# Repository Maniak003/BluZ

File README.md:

<!DOCTYPE html>
<html lang="en" data-color-mode="auto" data-light-theme="light" data-dark-theme="dark">
  <head>
    <meta charset="utf-8">
  </head>
    <body class="logged-in env-production page-responsive page-blob" style="word-wrap: break-word;">
      <p> BluZ Scintillation gamma spectrometer based on SiPM Sensl FC60035/FJ60035, Broadcom AFBR-S4N66C013, EQR15 11-6060D-S & NaI(Tl) or SrI2(Eu). Bluetooth 5.x<br>For discussion https://t.me/+mRf25RTZtPs3NTli</p>
      <a href=https://github.com/Maniak003/BluZ/releases/download/BluZ/BluZ-release.apk> Application in release </a>

    </body>
</html>

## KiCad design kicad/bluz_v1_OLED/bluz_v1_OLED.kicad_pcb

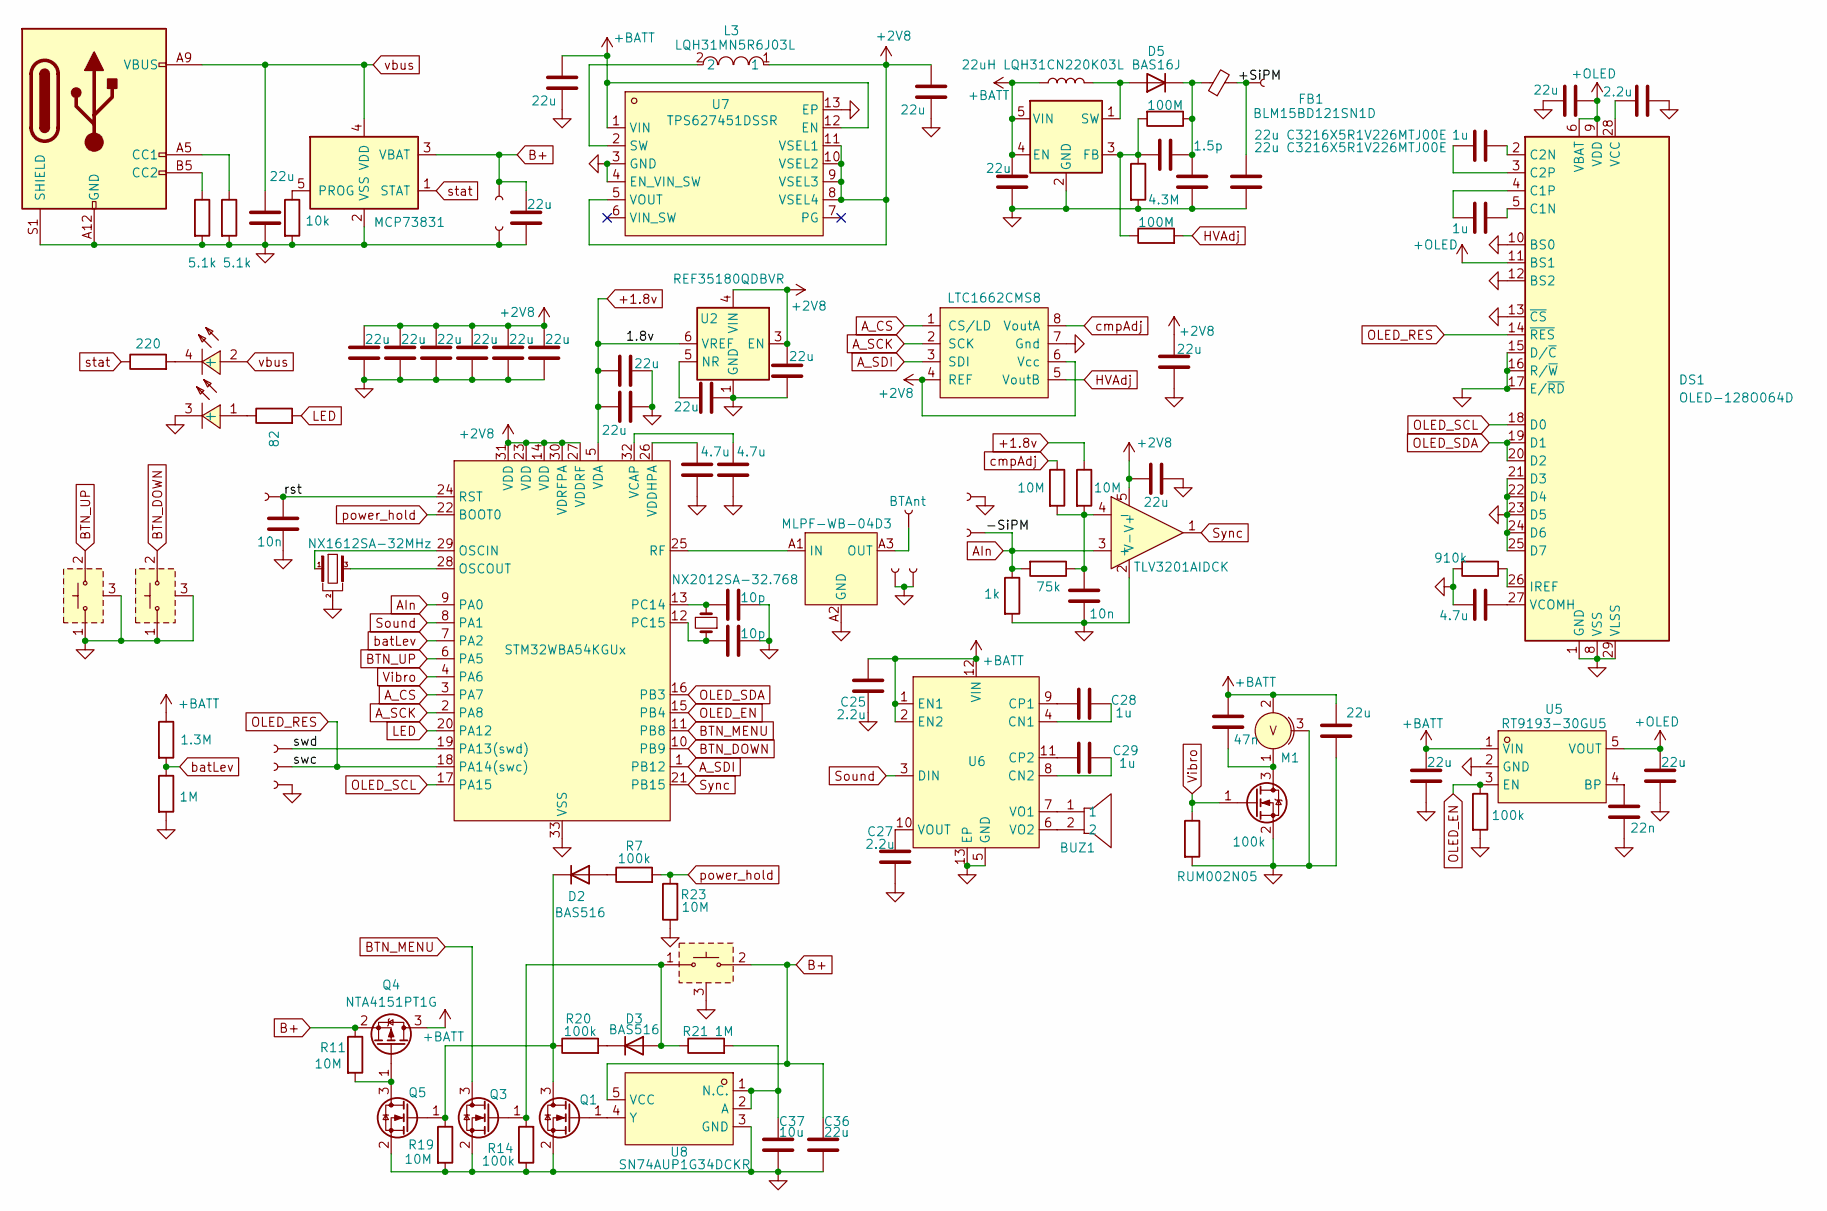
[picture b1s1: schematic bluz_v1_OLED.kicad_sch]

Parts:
BUZ1: PKMCS0909E4000-R1; BUZ-SMD_L9.0-W9.0_PKMCS0909E4000-R1; LCSC Part C910763
C1, C2, C3, C4, C5, C6, C8, C11, C13, C14, C15, C20, C23, C24, C30, C32, C33, C36, C39, C41, C42, C43: 22u; C_0402_1005Metric
C7, C17, C40: 4.7u; C_0402_1005Metric
C9: 1.5p; C_0402_1005Metric
C10, C25, C27: 2.2u; C_0402_1005Metric
C12, C18: 10n; C_0402_1005Metric
C16, C19: 22u C3216X5R1V226MTJ00E; C_1206_3216Metric
C21, C22: 10p; C_0402_1005Metric
C26: 47n; C_0402_1005Metric
C28, C29, C34, C35: 1u; C_0402_1005Metric
C31: 22n; C_0402_1005Metric
C37: 10u; C_0402_1005Metric
D1: STM32WBA54KGUx; QFN-32-1EP_5x5mm_P0.5mm_EP3.1x3.1mm
D2, D3: BAS516; D_SOD-523
D4: LTC1662CMS8; MSOP-8_3x3mm_P0.65mm
D5: BAS16J; D_SOD-323
D6: MLPF-WB-04D3
DS1: OLED-128O064D
FB1: BLM15BD121SN1D; R_0402_1005Metric
J1, J13: GND; conn_mini
J2, J3, J4, J5, J6, J7, J8, J10, J11: Conn; conn_mini
J9: USB_C_Receptacle_PowerOnly_6P; USB_C_Receptacle_GCT_USB4135-GF-A_6P_TopMnt_Horizontal
J12: BTAnt; conn_mini
L2: 22uH LQH31CN220K03L; L_1206_3216Metric_Pad1.42x1.75mm_HandSolder
L3: LQH31MN5R6J03L; L_1206_3216Metric_Pad1.42x1.75mm_HandSolder; LCSC Part C2044369
LED1: LTST-C195KGJRKT; LED-ARRAY-SMD_0603-4P-L1.6-W1.5-BR-RD; LCSC Part C125104
M1: Z3OC1T8219731; VibroMotor
Q1, Q3, Q5: NTA4153NT1G; SOT-723
Q2: RUM002N05; SOT-723
Q4: NTA4151PT1G; SOT-416_L1.6-W0.8-P1.00-LS1.6-BR
R1: 1.3M; R_0402_1005Metric
R2, R21: 1M; R_0402_1005Metric
R3: 10k; R_0402_1005Metric
R4: 220; R_0402_1005Metric
R5: 82; R_0402_1005Metric
R6: 1k; R_0402_1005Metric
R7, R12, R14, R20, R25: 100k; R_0402_1005Metric
R8, R9, R11, R19, R23: 10M; R_0402_1005Metric
R10: 75k; R_0402_1005Metric
R13, R16: 100M; R_0402_1005Metric
R15: 4.3M; R_0402_1005Metric
R17, R18: 5.1k; R_0402_1005Metric
R27: 910k; R_0402_1005Metric
SW4, SW5, SW6: SW-SMD_KMS2XXGXXX
U1: MCP73831; SOT-23-5
U2: REF35180QDBVR; SOT-23-6
U3: TLV3201AIDCK; TLV320x-SC70
U4: AP3015KTR; SOT-23-5
U5: RT9193-30GU5; SC-70-5_L2.0-W1.3-P0.65-LS2.1-BL; MPN RT9193-33GU5; LCSC Part C425797
U6: PAM8904EGPR; W-QFN2020-12_L2.0-W2.0-P0.40-TL-EP0.9; LCSC Part C510550
U7: TPS627451DSSR; WSON-12_L3.0-W2.0-P0.5-BL-EP; LCSC Part C2866178
U8: SN74AUP1G34DCKR; SC-70-5_L2.0-W1.3-P0.65-LS2.1-BL; MPN SN74AUP1G34DCKR; LCSC Part C2675656
Y1: NX1612SA-32MHz; NX1612SA
Y2: NX2012SA-32.768; Crystal_SMD_2012-2Pin_2.0x1.2mm

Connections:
+1.8v: C8.1, C23.1, D1.5 (VDA), R9.1, U2.6 (VREF)
+2V8: C1.1, C2.1, C3.1, C5.1, C6.1, C11.1, C13.1, C14.1, C30.1, C33.2, D1.14 (VDD), D1.23 (VDD), D1.27 (VDDRF), D1.30 (VDRFPA), D1.31 (VDD), D4.4 (REF), D4.6 (Vcc), L3.1, U2.3 (EN), U2.4 (VIN), U3.5 (V+), U7.5 (VOUT), U7.8 (VSEL4), U7.9 (VSEL3), U7.10 (VSEL2), U7.11 (VSEL1)
+BATT: C15.2, C24.2, C25.1, C26.1, C42.1, C43.1, L2.1, M1.2, Q4.3 (D), R1.1, U4.4 (EN), U4.5 (VIN), U5.1 (VIN), U6.1 (EN1), U6.2 (EN2), U6.12 (VIN), U7.1 (VIN), U7.12 (EN)
+OLED: C39.2, C41.1, DS1.6 (VBAT), DS1.9 (VDD), DS1.11 (BS1), U5.5 (VOUT)
/+SiPM: C19.2, FB1.2, J11.1
/rst: C18.2, D1.24 (RST), J2.1
/swd: D1.19 (PA13(swd)), J4.1
AIn: D1.9 (PA0), J8.1, R6.1, R10.2, U3.3 (+)
A_CS: D1.3 (PA7), D4.1 (CS/LD)
A_SCK: D1.2 (PA8), D4.2 (SCK)
A_SDI: D1.1 (PB12), D4.3 (SDI)
B+: C20.1, C36.1, J6.1, Q4.2 (S), R11.1, SW5.2, SW5.4, U1.3 (VBAT), U8.5 (VCC)
BTN_DOWN: D1.10 (PB9), SW6.2, SW6.4
BTN_MENU: D1.11 (PB8), Q3.3 (D)
BTN_UP: D1.6 (PA5), SW4.2, SW4.4
GND: C1.2, C2.2, C3.2, C4.2, C5.2, C6.2, C7.2, C8.2, C10.2, C11.2, C12.2, C13.2, C14.2, C15.1, C16.1, C17.2, C18.1, C19.1, C20.2, C21.2, C22.2, C23.2, C24.1, C25.2, C27.2, C30.2, C31.2, C32.2, C33.1, C36.2, C37.2, C39.1, C40.1, C41.2, C42.2, C43.2, D1.33 (VSS), D4.7 (Gnd), D6.A2 (GND), D6.B1 (GND), D6.B2 (GND), D6.B3 (GND), DS1.1 (GND), DS1.8 (VSS), DS1.10 (BS0), DS1.12 (BS2), DS1.13 (~CS), DS1.15 (D/~C), DS1.16 (R/~W), DS1.17 (E/~RD), DS1.21 (D3), DS1.22 (D4), DS1.23 (D5), DS1.24 (D6), DS1.25 (D7), DS1.29 (VLSS), DS1.30 (GND), J1.1, J3.1, J7.1, J9.A12 (GND), J9.B12 (GND), J9.S1 (SHIELD), J10.1, J13.1, LED1.3 (-), M1.3, Q1.2 (S), Q2.2 (S), Q3.2 (S), Q5.2 (S), R2.2, R3.2, R6.2, R12.2, R14.1, R15.2, R17.2, R18.2, R19.2, R23.1, R25.2, R27.2, SW4.1, SW4.3, SW4.5, SW5.3, SW6.1, SW6.3, SW6.5, U1.2 (VSS), U2.1 (GND), U2.2 (GND), U3.2 (V-), U4.2 (GND), U5.2 (GND), U6.5 (GND), U6.13 (EP), U7.3 (GND), U7.4 (EN_VIN_SW), U7.13 (EP), U8.3 (GND), Y1.2, Y1.4
HVAdj: D4.5 (VoutB), R13.2
LED: D1.20 (PA12), R5.2
unnamed: D1.29 (OSCIN), Y1.1
unnamed: D1.28 (OSCOUT), Y1.3
unnamed: C21.1, D1.13 (PC14), Y2.2
unnamed: C22.1, D1.12 (PC15), Y2.1
unnamed: D1.25 (RF), D6.A1 (IN)
unnamed: C7.1, D1.32 (VCAP)
unnamed: C17.1, D1.26 (VDDHPA)
unnamed: D2.2 (A), R7.1
unnamed: D2.1 (K), Q1.3 (D), Q5.1 (G), R19.1, R20.1
unnamed: D3.2 (A), Q3.1 (G), R14.2, R21.1, SW5.1, SW5.5
unnamed: D3.1 (K), R20.2
unnamed: D5.2 (A), L2.2, U4.1 (SW)
unnamed: C9.1, C16.2, D5.1 (K), FB1.1, R16.1
unnamed: D6.A3 (OUT), J12.1
unnamed: C35.2, DS1.5 (C1N)
unnamed: C35.1, DS1.4 (C1P)
unnamed: C34.2, DS1.2 (C2N)
unnamed: C34.1, DS1.3 (C2P)
unnamed: DS1.26 (IREF), R27.1
unnamed: C10.1, DS1.28 (VCC)
unnamed: C40.2, DS1.27 (VCOMH)
unnamed: J9.A5 (CC1), R17.1
unnamed: J9.B5 (CC2), R18.1
unnamed: LED1.1 (+), R5.1
unnamed: LED1.4 (-), R4.2
unnamed: Q1.1 (G), U8.4 (Y)
unnamed: C26.2, M1.1, Q2.3 (D)
unnamed: Q4.1 (G), Q5.3 (D), R11.2
unnamed: R3.1, U1.5 (PROG)
unnamed: C32.1, U2.5 (NR)
unnamed: C12.1, R8.2, R9.2, R10.1, U3.4 (-)
unnamed: C9.2, R13.1, R15.1, R16.2, U4.3 (FB)
unnamed: C31.1, U5.4 (BP)
unnamed: C28.2, U6.4 (CN1)
unnamed: C29.1, U6.8 (CN2)
unnamed: C28.1, U6.9 (CP1)
unnamed: C29.2, U6.11 (CP2)
unnamed: BUZ1.1, U6.7 (VO1)
unnamed: BUZ1.2, U6.6 (VO2)
unnamed: C27.1, U6.10 (VOUT)
unnamed: L3.2, U7.2 (SW)
unnamed: C37.1, R21.2, U8.1 (N.C.), U8.2 (A)
OLED_EN: D1.15 (PB4), R25.1, U5.3 (EN)
OLED_RES: D1.18 (PA14(swc)), DS1.14 (~RES), J5.1
OLED_SCL: D1.17 (PA15), DS1.18 (D0)
OLED_SDA: D1.16 (PB3), DS1.19 (D1), DS1.20 (D2)
Sound: D1.8 (PA1), U6.3 (DIN)
Sync: D1.21 (PB15), U3.1
Vibro: D1.4 (PA6), Q2.1 (G), R12.1
batLev: D1.7 (PA2), R1.2, R2.1
cmpAdj: D4.8 (VoutA), R8.1
power_hold: D1.22 (BOOT0), R7.2, R23.2
stat: R4.1, U1.1 (STAT)
vbus: C4.1, J9.A9 (VBUS), J9.B9 (VBUS), LED1.2 (+), U1.4 (VDD)

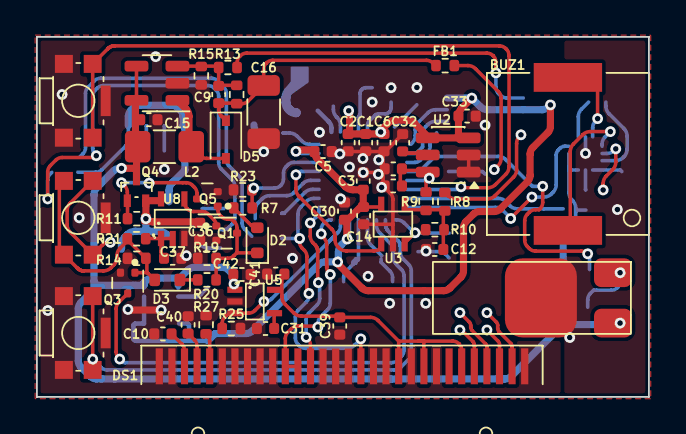
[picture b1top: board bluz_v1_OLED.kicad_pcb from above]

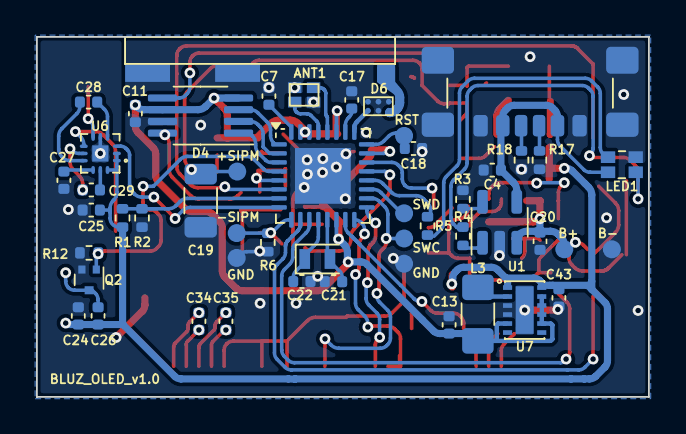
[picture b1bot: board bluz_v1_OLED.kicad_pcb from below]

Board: 2 copper layers, 34.0 x 20.0 mm, 110 parts (50 on the bottom side), 72 nets.

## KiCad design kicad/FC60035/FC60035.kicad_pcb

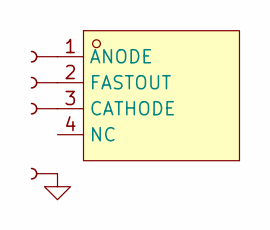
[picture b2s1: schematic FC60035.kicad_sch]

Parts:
J1, J2, J3, J4: Conn; SMD-CONN
U1: MICROFC-60035-SMT-TR; OPTO-SMD_4P-MICROFC-60035-SMT-TR; MPN MICROFC-60035-SMT-TR; LCSC Part C603293

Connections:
GND: J4.1
unnamed: J2.1, U1.1 (ANODE)
unnamed: J1.1, U1.3 (CATHODE)
unnamed: J3.1, U1.2 (FASTOUT)

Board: 2 copper layers, 5 parts (1 on the bottom side), 3 nets, no tracks yet.

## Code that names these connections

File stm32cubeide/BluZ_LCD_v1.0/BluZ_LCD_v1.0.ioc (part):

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Mcu.Name=STM32WBA54KGUx
Mcu.Package=UFQFPN32
Mcu.UserName=STM32WBA54KGUx
PA0.GPIOParameters=GPIO_Label
PA0.GPIO_Label=AIn
PA0.Mode=IN9
PA0.Signal=ADC4_IN9
PA1.GPIOParameters=GPIO_Label
PA1.GPIO_Label=SOUND
PA1.Signal=S_LPTIM2_CH2
PA12.GPIOParameters=GPIO_Label
PA12.GPIO_Label=LED
PA12.Signal=GPIO_Output
PA13\ (JTMS/SWDIO).GPIOParameters=GPIO_Label
PA13\ (JTMS/SWDIO).GPIO_Label=DISPLAY_ENABLE
PA13\ (JTMS/SWDIO).Signal=GPIO_Output
PA14\ (JTCK/SWCLK).GPIOParameters=GPIO_Label
PA14\ (JTCK/SWCLK).GPIO_Label=DISPLAY_CS
PA14\ (JTCK/SWCLK).Signal=GPIO_Output
PA15\ (JTDI).GPIOParameters=GPIO_Label
PA15\ (JTDI).GPIO_Label=DISPLAY_SI
PA15\ (JTDI).Mode=TX_Only_Simplex_Unidirect_Master
PA15\ (JTDI).Signal=SPI1_MOSI
PA2.GPIOParameters=GPIO_Label
PA2.GPIO_Label=batLev
PA2.Mode=IN7
PA2.Signal=ADC4_IN7
PA5.GPIOParameters=GPIO_Label
PA5.GPIO_Label=BTN_UP
PA5.Signal=GPIO_Input
PA6.GPIOParameters=GPIO_Label
PA6.GPIO_Label=VIBRO
PA6.Signal=GPIO_Output
PA7.GPIOParameters=GPIO_Label
PA7.GPIO_Label=A_CS
PA7.Signal=GPIO_Output
PA8.GPIOParameters=GPIO_Label
PA8.GPIO_Label=A_SCK
PA8.Signal=GPIO_Output
PB12.GPIOParameters=GPIO_Label
PB12.GPIO_Label=A_DATA
PB12.Signal=GPIO_Output
PB15.GPIOParameters=GPIO_Label,GPIO_ModeDefaultEXTI
PB15.GPIO_Label=Sync
PB15.GPIO_ModeDefaultEXTI=GPIO_MODE_IT_RISING
PB15.Signal=GPXTI15
PB3\ (JTDO/TRACESWO).GPIOParameters=GPIO_Label
PB3\ (JTDO/TRACESWO).GPIO_Label=DISPLAY_EXTCOMIN
PB3\ (JTDO/TRACESWO).Signal=S_TIM1_CH4
PB4\ (NJTRST).GPIOParameters=GPIO_Label
PB4\ (NJTRST).GPIO_Label=DISPLAY_SLC
PB4\ (NJTRST).Mode=TX_Only_Simplex_Unidirect_Master
PB4\ (NJTRST).Signal=SPI1_SCK
PB8.GPIOParameters=GPIO_Label
PB8.GPIO_Label=BTN_MENU
PB8.Signal=GPIO_Input
PB9.GPIOParameters=GPIO_Label
PB9.GPIO_Label=BTN_DOWN
PB9.Signal=GPIO_Input
PC14-OSC32_IN.Mode=LSE-External-Oscillator
PC14-OSC32_IN.Signal=RCC_OSC32_IN
PC15-OSC32_OUT.Mode=LSE-External-Oscillator
PC15-OSC32_OUT.Signal=RCC_OSC32_OUT
PH3-BOOT0.GPIOParameters=GPIO_Label
PH3-BOOT0.GPIO_Label=POWER_HOLD
PH3-BOOT0.Signal=GPIO_Output
RCC.HSESYSFreq_VALUE=16000000
RCC.HSE_VALUE=32000000
RCC.SYSCLKFreq_VALUE=16000000
board=custom

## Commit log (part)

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2025-10-07 изменено: Android/BluZ_LPM/app/build.gradle изменено: Android/BluZ_LPM/app/src/main/AndroidManifest.xml изменено: Android/BluZ_LPM/app/src/main/java/ru/starline/bluz/MainActivity.kt новый файл: Andro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
2025-10-08 изменено: Android/BluZ_LPM/app/src/main/AndroidManifest.xml изменено: Android/BluZ_LPM/app/src/main/java/ru/starline/bluz/MainActivity.kt изменено: Android/BluZ_LPM/app/src/main/java/ru/starline/bluz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
2025-10-10 изменено: Android/BluZ_LPM/app/src/main/java/ru/starline/bluz/NumberFragment.kt изменено: Android/BluZ_LPM/app/src/main/java/ru/starline/bluz/data/dao/DosimeterDao.kt изменено: Android/BluZ_LPM/app/s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
2025-10-14 удалено: kicad/bluz_v1_typec/bluz_v1-backups/bluz_v1-2025-01-22_110710.zip удалено: kicad/bluz_v1_typec/bluz_v1-backups/bluz_v1-2025-01-28_102500.zip удалено: kicad/bluz_v1_typec/bluz_v1-backups/bluz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
2025-10-14 новый файл: Android/BluZ_LPM/app/src/main/java/ru/starline/bluz/utils/Task.kt
2025-10-17 изменено: Android/BluZ_LPM/app/src/main/java/ru/starline/bluz/NumberFragment.kt изменено: Android/BluZ_LPM/app/src/main/java/ru/starline/bluz/bgService.kt
2025-10-17 изменено: Android/BluZ_LPM/app/src/main/java/ru/starline/bluz/NumberFragment.kt
2025-10-20 удалено: Documents/rm0493-multiprotocol-wireless-bluetooth-lowenergy-and-ieee802154-stm32wba5xxx-armbased-32bit-mcus-stmicroelectronics.pdf
2025-10-31 изменено: Android/BluZ_LPM/app/build.gradle изменено: Android/BluZ_LPM/app/src/main/AndroidManifest.xml изменено: Android/BluZ_LPM/app/src/main/java/ru/starline/bluz/MainActivity.kt изменено: Android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
2025-11-03 изменено: FreeCAD/BluZ_cover_10x40_type-c.FCStd
2025-11-06 изменено: Android/BluZ_LPM/app/src/main/java/ru/starline/bluz/MainActivity.kt изменено: Android/BluZ_LPM/app/src/main/java/ru/starline/bluz/NumberFragment.kt изменено: Android/BluZ_LPM/app/src/main/j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
2025-11-13 изменено: Android/BluZ_LPM/BluZ/src/main/java/ru/starline/bluz/BluetoothInterface.kt изменено: Android/BluZ_LPM/BluZ/src/main/java/ru/starline/bluz/NumberFragment.kt изменено: Android/BluZ_LPM/BluZ/s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
2025-11-14 изменено: Android/BluZ_LPM/BluZ/src/main/java/ru/starline/bluz/drawDozimeter.kt изменено: Android/BluZ_LPM/BluZ/src/main/java/ru/starline/bluz/drawExmple.kt изменено: Android/BluZ_LPM/BluZ/src/main/j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
2025-11-14 удалено: kicad/bluz_v1_typec/bluz_v1-backups/bluz_v1-2025-06-09_170559.zip удалено: kicad/bluz_v1_typec/bluz_v1-backups/bluz_v1-2025-06-09_180824.zip удалено: kicad/bluz_v1_typec/bluz_v1-backups/bluz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
2025-11-15 изменено: Android/BluZ_LPM/.idea/gradle.xml изменено: Android/BluZ_LPM/.idea/misc.xml изменено: Android/BluZ_LPM/BluZ/src/main/java/ru/starline/bluz/BluetoothInterface.kt изменено: Android/BluZ_LPM/B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
2025-11-16 изменено: Android/BluZ_LPM/BluZ/build.gradle изменено: Android/BluZ_LPM/BluZ/src/main/java/ru/starline/bluz/NumberFragment.kt изменено: Android/BluZ_LPM/BluZ/src/main/java/ru/starline/bluz/bgService.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
2025-11-17 изменено: stm32cubeide/BluZ_LPM/.mxproject изменено: stm32cubeide/BluZ_LPM/Core/Inc/main.h изменено: stm32cubeide/BluZ_LPM/Release/BluZ_LPM.elf
2025-11-17 изменено: stm32cubeide/BluZ_LPM/Release/BluZ_LPM.elf изменено: stm32cubeide/BluZ_LPM/STM32_WPAN/App/app_ble.c изменено: stm32cubeide/BluZ_LPM/STM32_WPAN/App/bluz_app.c
2025-11-18 изменено: FreeCAD/BluZ_cover_10x10.FCStd изменено: FreeCAD/BluZ_cover_10x10.stl изменено: FreeCAD/BluZ_cover_10x40_type-c.FCStd
2025-11-18 изменено: Android/BluZ_LPM/BluZ/src/main/java/ru/starline/bluz/NumberFragment.kt изменено: Android/BluZ_LPM/BluZ/src/main/res/layout/setup_layout.xml изменено: Android/BluZ_LPM/BluZ/src/main/res/valu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
2025-11-19 изменено: stm32cubeide/BluZ_LPM/Core/Inc/main.h изменено: stm32cubeide/BluZ_LPM/STM32_WPAN/App/bluz_app.c
    изменено: stm32cubeide/BluZ_LPM/Core/Inc/main.h
    удалено: stm32cubeide/BluZ_LPM/Release/BluZ_LPM.elf
    изменено: stm32cubeide/BluZ_LPM/STM32_WPAN/App/bluz_app.c
2025-11-19 изменено: stm32cubeide/BluZ_LPM/Core/Src/main.c
2025-11-20 изменено: stm32cubeide/BluZ_LPM/Core/Inc/app_conf.h изменено: stm32cubeide/BluZ_LPM/Core/Inc/main.h изменено: stm32cubeide/BluZ_LPM/Core/Src/main.c изменено: stm32cubeide/BluZ_LPM/Release/BluZ_LPM.elf
2025-11-21 изменено: Android/BluZ_LPM/BluZ/src/main/AndroidManifest.xml изменено: Android/BluZ_LPM/BluZ/src/main/java/ru/starline/bluz/BluetoothInterface.kt изменено: Android/BluZ_LPM/BluZ/src/main/java/ru/star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
2025-11-22 изменено: Android/BluZ_LPM/BluZ/src/main/java/ru/starline/bluz/BluetoothInterface.kt изменено: kicad/bluz_v1_typec/bluz_v1.kicad_prl
2025-11-22 изменено: Android/BluZ_LPM/BluZ/src/main/java/ru/starline/bluz/MainActivity.kt
2025-11-25 изменено: Android/BluZ_LPM/BluZ/src/main/java/ru/starline/bluz/MainActivity.kt изменено: kicad/bluz_v1_typec/bluz_v1.kicad_pcb изменено: kicad/bluz_v1_typec/bluz_v1.kicad_sch
2025-12-13 изменено: FreeCAD/BluZ_case_2_10x40_type-c.FCStd изменено: FreeCAD/BluZ_case_2_10x40_type-c.stl новый файл: FreeCAD/BluZ_cover_2_10x10_type-c.FCStd новый файл: FreeCAD/BluZ_cover_2_10x10_type-c.stl и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
2025-12-15 удалено: kicad/bluz_v1_typec/bluz_v1-backups/bluz_v1-2025-08-04_165055.zip
2025-12-20 изменено: FreeCAD/BluZ_case_2_10x40_type-c.FCStd изменено: FreeCAD/BluZ_case_2_10x40_type-c.stl
2025-12-21 изменено: stm32cubeide/BluZ_LPM/Core/Inc/main.h изменено: stm32cubeide/BluZ_LPM/Release/BluZ_LPM.elf
2025-12-26 изменено: Android/BluZ_LPM/BluZ/src/main/java/ru/starline/bluz/MainActivity.kt изменено: Android/BluZ_LPM/BluZ/src/main/java/ru/starline/bluz/drawLogs.kt изменено: Android/BluZ_LPM/BluZ/src/main/java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
2025-12-26 новый файл: Android/BluZ_archive/.gitignore новый файл: Android/BluZ_archive/.idea/.gitignore новый файл: Android/BluZ_archive/.idea/.name новый файл: Android/BluZ_archive/.idea/codeStyles/Project.xm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
2026-01-23 изменено: FreeCAD/BluZ_cover_2_10x10_type-c.FCStd изменено: FreeCAD/BluZ_cover_2_10x10_type-c.stl изменено: kicad/bluz_v1_typec/bluz_v1.kicad_prl изменено: kicad/bluz_v1_typec/gerber/BluZ.zip
2026-01-27 изменено: kicad/bluz_v1_typec/bom/ibom.html
2026-01-27 изменено: kicad/bluz_v1_typec/bluz_v1.kicad_pcb изменено: kicad/bluz_v1_typec/bluz_v1.kicad_sch изменено: kicad/bluz_v1_typec/bom/ibom.html
2026-01-30 изменено: kicad/bluz_v1_typec/fp-info-cache
2026-01-30 изменено: Android/BluZ_LPM/BluZ/src/main/java/ru/starline/bluz/MLEM.kt изменено: Android/BluZ_LPM/BluZ/src/main/java/ru/starline/bluz/MainActivity.kt изменено: Android/BluZ_LPM/BluZ/src/main/java/ru/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
2026-02-06 изменено: Android/BluZ_LPM/BluZ/src/main/java/ru/starline/bluz/MLEM.kt изменено: Android/BluZ_LPM/BluZ/src/main/java/ru/starline/bluz/NumberFragment.kt изменено: Android/BluZ_LPM/BluZ/src/main/java/r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
2026-02-10 изменено: Android/BluZ_LPM/BluZ/src/main/java/ru/starline/bluz/MLEM.kt изменено: Android/BluZ_LPM/BluZ/src/main/java/ru/starline/bluz/NumberFragment.kt изменено: Android/BluZ_LPM/BluZ/src/main/java/r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
2026-02-11 изменено: Android/BluZ_LPM/BluZ/src/main/java/ru/starline/bluz/MLEM.kt изменено: Android/BluZ_LPM/BluZ/src/main/java/ru/starline/bluz/NumberFragment.kt изменено: Android/BluZ_LPM/BluZ/src/main/java/r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
2026-02-15 новый файл: kicad/bluz_v2_typec/2024-05-07_07-39-39.kicad_sym новый файл: kicad/bluz_v2_typec/CSPG6_1P05X1P65_STM-L.kicad_mod новый файл: kicad/bluz_v2_typec/CSPG6_1P05X1P65_STM-M.kicad_mod новый фай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
2026-02-16 изменено: kicad/bluz_v2_typec/bluz_v1.kicad_pcb изменено: kicad/bluz_v2_typec/bluz_v1.kicad_prl изменено: kicad/bluz_v2_typec/bluz_v1.kicad_pro изменено: kicad/bluz_v2_typec/bluz_v1.kicad_sch
2026-02-18 изменено: Android/BluZ_LPM/BluZ/src/main/java/ru/starline/bluz/NumberFragment.kt изменено: Android/BluZ_LPM/BluZ/src/main/java/ru/starline/bluz/drawSpecter.kt изменено: Android/BluZ_LPM/BluZ/src/main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
2026-02-20 удалено: kicad/bluz_v2_typec/bluz_v1-backups/bluz_v1-2025-11-02_134433.zip удалено: kicad/bluz_v2_typec/bluz_v1-backups/bluz_v1-2025-11-02_135440.zip изменено: kicad/bluz_v2_typec/bluz_v1.kicad_pcb и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
2026-02-23 изменено: stm32cubeide/BluZ_LPM/.project удалено: stm32cubeide/BluZ_LPM/BluZ_LPM.ioc изменено: stm32cubeide/BluZ_LPM/programm.sh
2026-03-06 изменено: Android/BluZ_LPM/BluZ/src/main/java/ru/starline/bluz/BluetoothInterface.kt изменено: Android/BluZ_LPM/BluZ/src/main/java/ru/starline/bluz/drawLogs.kt изменено: Android/BluZ_LPM/BluZ/src/mai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
2026-03-06 новый файл: stm32cubeide/BluZ_LPM/Release/BluZ_LPM_v1.elf изменено: stm32cubeide/BluZ_LPM_v2/.settings/language.settings.xml
2026-03-22 изменено: Android/BluZ_LPM/BluZ/src/main/java/ru/starline/bluz/NumberFragment.kt изменено: kicad/bluz_v1_typec/bluz_v1.kicad_pcb изменено: stm32cubeide/BluZ_LPM/BluZ_LPM_v1.ioc изменено: stm32cubeide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
2026-04-02 изменено: Android/BluZ_LPM/BluZ/src/main/java/ru/starline/bluz/BluetoothInterface.kt изменено: Android/BluZ_LPM/BluZ/src/main/java/ru/starline/bluz/NumberFragment.kt изменено: Android/BluZ_LPM/BluZ/s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
2026-04-10 изменено: Android/BluZ_LPM/BluZ/src/main/AndroidManifest.xml изменено: Android/BluZ_LPM/BluZ/src/main/java/ru/starline/bluz/NumberFragment.kt изменено: Android/BluZ_LPM/BluZ/src/main/java/ru/starline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
2026-04-13 новый файл: Documents/setup_screen.png
2026-04-15 удалено: kicad/bluz_v2_typec/bluz_v1-backups/bluz_v1-2026-01-23_152519.zip изменено: kicad/bluz_v2_typec/bluz_v1.kicad_pcb изменено: kicad/bluz_v2_typec/bluz_v1.kicad_prl изменено: kicad/bluz_v2_type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
2026-04-29 изменено: Android/BluZ_LPM/BluZ/src/main/java/ru/starline/bluz/BluetoothInterface.kt изменено: Android/BluZ_LPM/BluZ/src/main/java/ru/starline/bluz/MainActivity.kt изменено: Android/BluZ_LPM/BluZ/src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
2026-05-07 изменено: Android/BluZ_LPM/BluZ/src/main/AndroidManifest.xml изменено: Android/BluZ_LPM/BluZ/src/main/java/ru/starline/bluz/MainActivity.kt изменено: Android/BluZ_LPM/BluZ/src/main/java/ru/starline/b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
2026-05-08 новый файл: Documents/EnergComp/Geant4/NaI_10x10/CMakeLists.txt новый файл: Documents/EnergComp/Geant4/NaI_10x10/GNUmakefile новый файл: Documents/EnergComp/Geant4/NaI_10x10/History новый файл: Docum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
2026-05-09 удалено: kicad/bluz_v2_typec/bluz_v1-backups/bluz_v1-2026-02-14_112253.zip удалено: kicad/bluz_v2_typec/bluz_v1-backups/bluz_v1-2026-02-14_192355.zip изменено: kicad/bluz_v2_typec/bluz_v1.kicad_pcb и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
2026-05-12 изменено: Documents/EnergComp/Geant4/NaI_10x10/build/NaI_response_h1_Edep.csv изменено: Documents/EnergComp/Geant4/NaI_10x10/build/exec.txt изменено: Documents/EnergComp/Geant4/NaI_10x10/build/genera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
2026-05-13 новый файл: Documents/EnergComp/Geant4/CsI_10x10x30/CMakeLists.txt новый файл: Documents/EnergComp/Geant4/CsI_10x10x30/GNUmakefile новый файл: Documents/EnergComp/Geant4/CsI_10x10x30/History новый фа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
2026-05-22 изменено: Android/BluZ_LPM/BluZ/src/main/java/ru/starline/bluz/MainActivity.kt изменено: kicad/bluz_v2_typec/fp-info-cache
2026-05-22 изменено: Documents/EnergComp/Geant4/NaI_10x10/build/CMakeFiles/exampleB1.dir/src/RunAction.cc.o изменено: Documents/EnergComp/Geant4/NaI_10x10/build/exampleB1 изменено: Documents/EnergComp/Geant4/Na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
2026-05-30 изменено: kicad/bluz_v2_typec/bluz_v1.kicad_pro
2026-06-01 новый файл: Android/BluZ_v2/.claude/settings.local.json новый файл: Android/BluZ_v2/.idea/.gitignore новый файл: Android/BluZ_v2/.idea/BluZ_v2.iml новый файл: Android/BluZ_v2/.idea/caches/deviceStrea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
2026-06-02 удалено: Android/BluZ_v2/BluZ
2026-06-02 изменено: Android/BluZ_v2/BluZ/Android/BluZ_LPM/.idea/vcs.xml изменено: Android/BluZ_v2/BluZ/Android/BluZ_LPM/BluZ/src/main/java/ru/starline/bluz/AutoCalibrationController.kt изменено: Android/BluZ_v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
2026-06-06 новый файл: FreeCAD/BluZ_case_3_type-c.FCStd новый файл: FreeCAD/BluZ_case_3_type-c.stl новый файл: FreeCAD/BluZ_cover_2_10x10x40_type-c.FCStd новый файл: FreeCAD/BluZ_cover_2_10x10x40_type-c.stl
2026-06-09 изменено: Android/BluZ_v2/BluZ/Android/BluZ_LPM/BluZ/src/main/java/ru/starline/bluz/BluetoothInterface.kt изменено: Android/BluZ_v2/BluZ/Android/BluZ_LPM/BluZ/src/main/java/ru/starline/bluz/DeviceFra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
2026-06-12 изменено: FreeCAD/BluZ_case_3_type-c.FCStd изменено: FreeCAD/BluZ_case_3_type-c.stl
2026-06-12 изменено: "Documents/\320\232\320\276\320\275\321\206\320\265\320\275\321\202\321\200\320\270\321\200\320\276\320\262\320\260\320\275\320\270\320\265 \320\276\320\261\321\200\320\260\320\267\321\206\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
2026-06-14 изменено: Android/BluZ_LPM/.idea/misc.xml удалено: Android/BluZ_v2/BluZ/Android/BluZ_LPM/.idea/deploymentTargetSelector.xml изменено: Android/BluZ_v2/BluZ/Android/BluZ_LPM/.idea/misc.xml изменено: An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
2026-06-21 изменено: stm32cubeide/BluZ_LPM/Core/Inc/main.h изменено: stm32cubeide/BluZ_LPM/Core/Src/main.c изменено: stm32cubeide/BluZ_LPM/Release/BluZ_LPM_v1.elf
